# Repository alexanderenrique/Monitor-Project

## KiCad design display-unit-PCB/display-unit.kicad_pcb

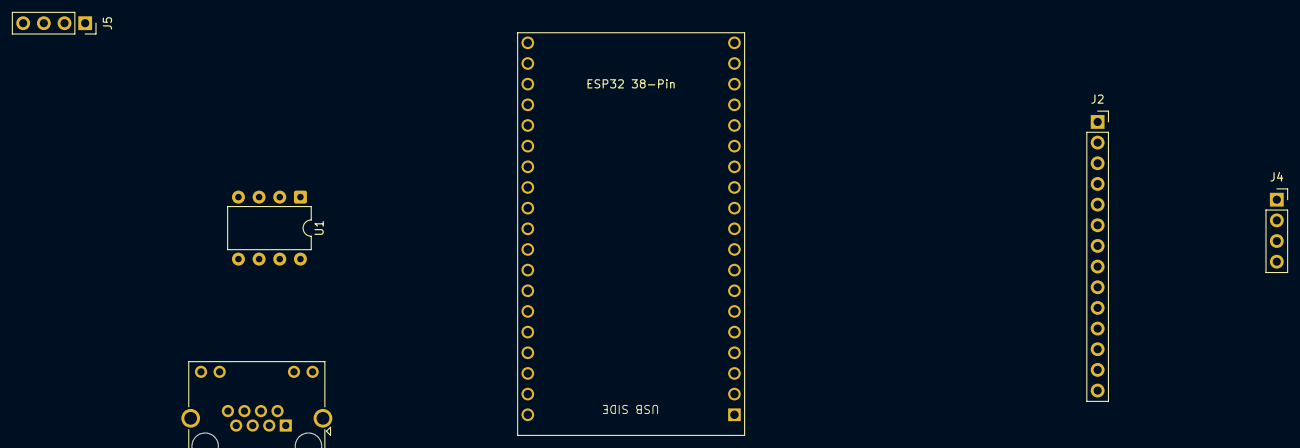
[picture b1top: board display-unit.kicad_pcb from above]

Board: 2 copper layers, 6 parts (0 on the bottom side), 18 nets, no tracks yet.

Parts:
J1: RJ45_LED_Shielded; RJ45_Amphenol_RJHSE538X
J2: Display; TFT-14pin-Alex
J3: ESP32 38-Pin; ESP32-DEVKITC-32UE-Alex
J4: SD_Card; PinSocket_1x04_P2.54mm_Vertical
J5: RTC; PinSocket_1x04_P2.54mm_Vertical
U1: MAX3485; DIP-8_W7.62mm

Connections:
unnamed: J1.1, J3.5V (Pin_15)
unnamed: J2.SCK (14), J2.T_CLK (Pin_9), J3.18 (Pin_5), J4.CLK (Pin_4)
unnamed: J2.GND (Pin_2), J3.GND (3.3)
unnamed: J2.CS (Pin_3), J3.16 (Pin_8)
unnamed: J2.RST (Pin_4), J3.17 (Pin_7)
unnamed: J2.T_CS (Pin_10), J3.27 (Pin_23)
unnamed: J2.MOSI (Pin_6), J2.T_MOSI (Pin_11), J3.23 (Pin_2), J4.MOSI (Pin_2)
unnamed: J2.T_MISO (Pin_12), J3.19 (Pin_4), J4.MISO (Pin_3)
unnamed: J1.2, J1.4, J1.6, J5.GND (Pin_4)
unnamed: J3.33 (Pin_27), J4.CS (Pin_1)
unnamed: J3.22 (3.3), J5.SCL (Pin_1)
unnamed: J3.21 (Pin_2), J5.SDA (Pin_2)
unnamed: J2.VCC, J3.3.3V, J5.VCC (Pin_3), U1.8 (VCC)
unnamed: J1.5, U1.6 (A)
unnamed: J1.3, U1.7 (B)
unnamed: J3.TX (Pin_2), U1.4 (D)
unnamed: U1.2 (~RE), U1.3 (DE)
unnamed: J3.RX (3.3), U1.1 (R)

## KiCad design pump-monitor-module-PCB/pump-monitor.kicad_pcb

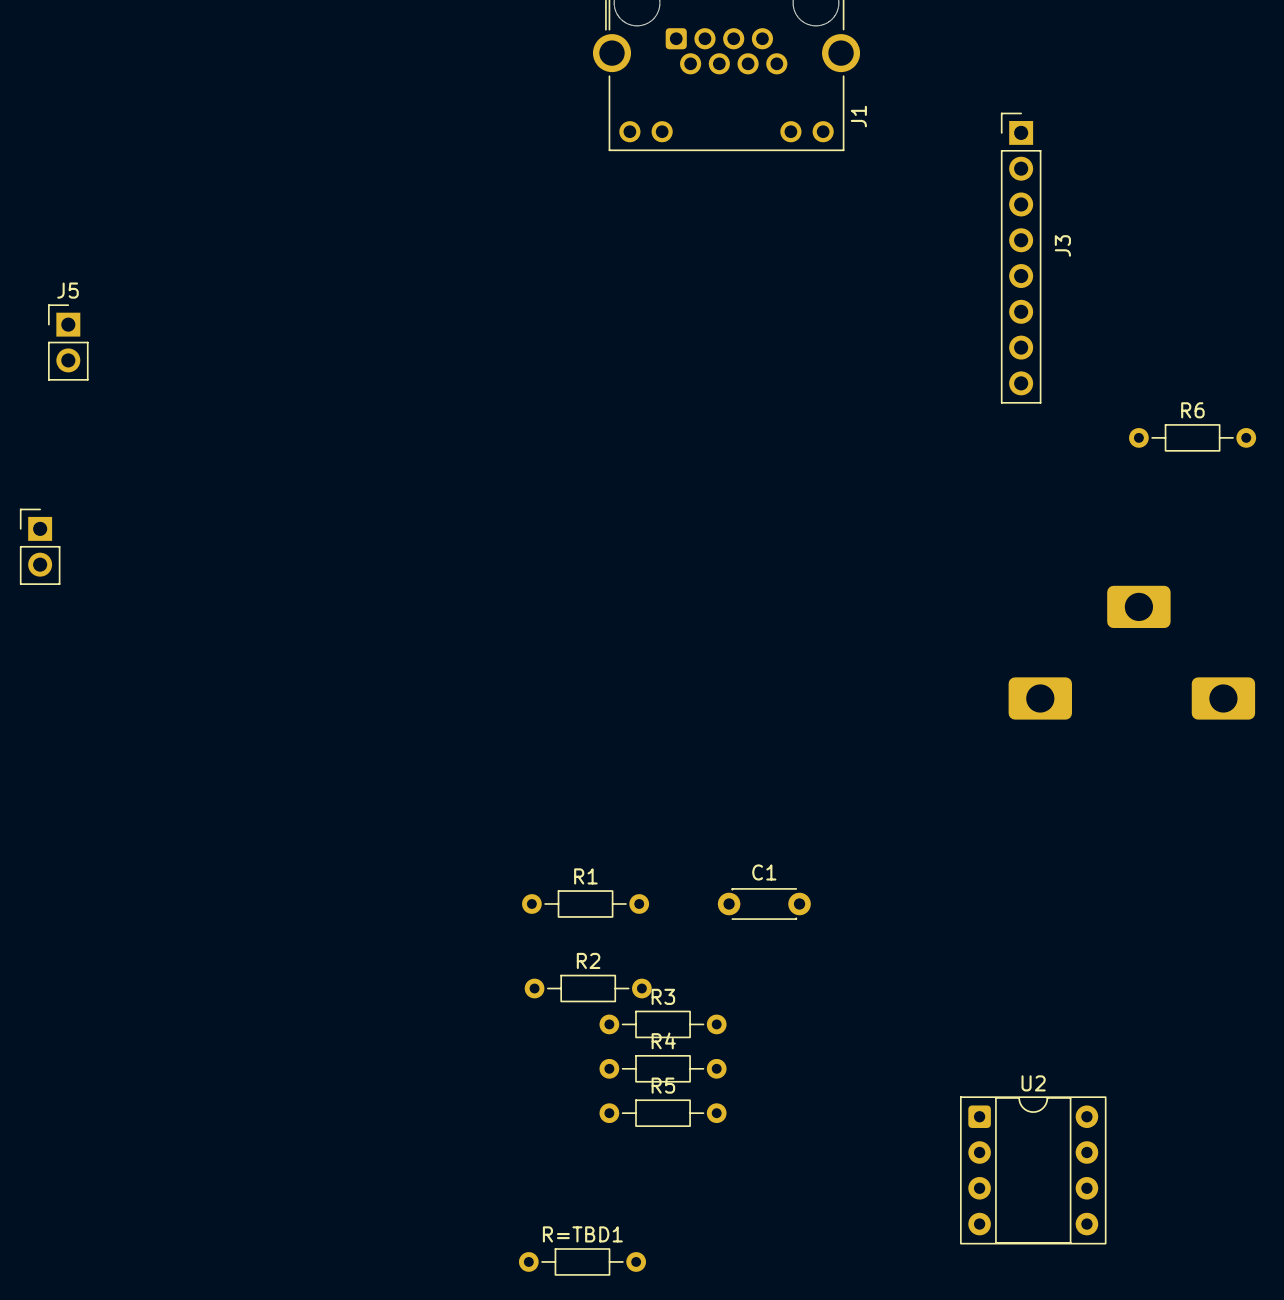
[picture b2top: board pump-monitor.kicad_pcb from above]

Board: 2 copper layers, 14 parts (0 on the bottom side), 11 nets, no tracks yet.

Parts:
C1: 10nF; C_Disc_D4.3mm_W1.9mm_P5.00mm
J1: RJ45_LED; RJ45_Connfly_DS1128-09-S8xx-S_Horizontal
J2: Thermistor_2; PinHeader_1x02_P2.54mm_Vertical
J3: SEED C3; MPU-6050-Alex254
J4: CT_jack_input; 3.5mm_jack_alex
J5: Thermistor_1; PinHeader_1x02_P2.54mm_Vertical
R1, R2, R3: R_US; R_Axial_DIN0204_L3.6mm_D1.6mm_P7.62mm_Horizontal
R4: 10; R_Axial_DIN0204_L3.6mm_D1.6mm_P7.62mm_Horizontal
R5: 100; R_Axial_DIN0204_L3.6mm_D1.6mm_P7.62mm_Horizontal
R6: 10k; R_Axial_DIN0204_L3.6mm_D1.6mm_P7.62mm_Horizontal
R=TBD1: R_US; R_Axial_DIN0204_L3.6mm_D1.6mm_P7.62mm_Horizontal
U2: MCP6002-xP; DIP-8_W7.62mm_Socket

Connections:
unnamed: J1.5, U2.7
unnamed: J1.6, J2.1, R=TBD1.1
unnamed: C1.1, J1.1, J1.12, J2.2, J3.3.3V (Pin_1), J5.2, R3.1, U2.8 (V+)
unnamed: J1.2, J1.11, J3.GND (Pin_2), R1.2, R=TBD1.2
unnamed: J1.3, J3.SCL (Pin_3)
unnamed: J1.4, J3.SDA (Pin_4)
unnamed: J1.7, J5.1, R1.1
unnamed: J4.L, R2.2, R3.2, U2.3 (+)
unnamed: R6.2, U2.1, U2.2 (-)
unnamed: J4.K, R6.1, U2.6 (-)
unnamed: R2.1, U2.4 (V-)

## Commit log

2025-12-08 created main
2025-12-09 working script, it was wiring
2025-12-17 Add KiCad PCB files and pump monitor module code
2025-12-17 merged projects
2025-12-17 cleaned up duplicates
2025-12-17 working scripts
2025-12-18 checkpoint, pushed and working
2025-12-18 working screen demo
2025-12-19 moved to LVGL 8.3 fixed color and rotation
2025-12-30 first push
2025-12-30 she complies
2026-01-07 working display code, added SD card logging, value limits, error clearing
2026-01-08 added dummy pump module code
2026-01-09 bit bang SPI working, don't love it
2026-01-10 UART saves the day
2026-01-14 time works, UART
2026-01-14 checkpoint with year and time
2026-01-15 RTC working, check point
2026-01-16 working SD card pt2
2026-01-16 simplified sd card
2026-01-16 checkpoint
2026-01-16 done for today
2026-01-28 trying to migrate
2026-01-29 migration, added cheat sheet
